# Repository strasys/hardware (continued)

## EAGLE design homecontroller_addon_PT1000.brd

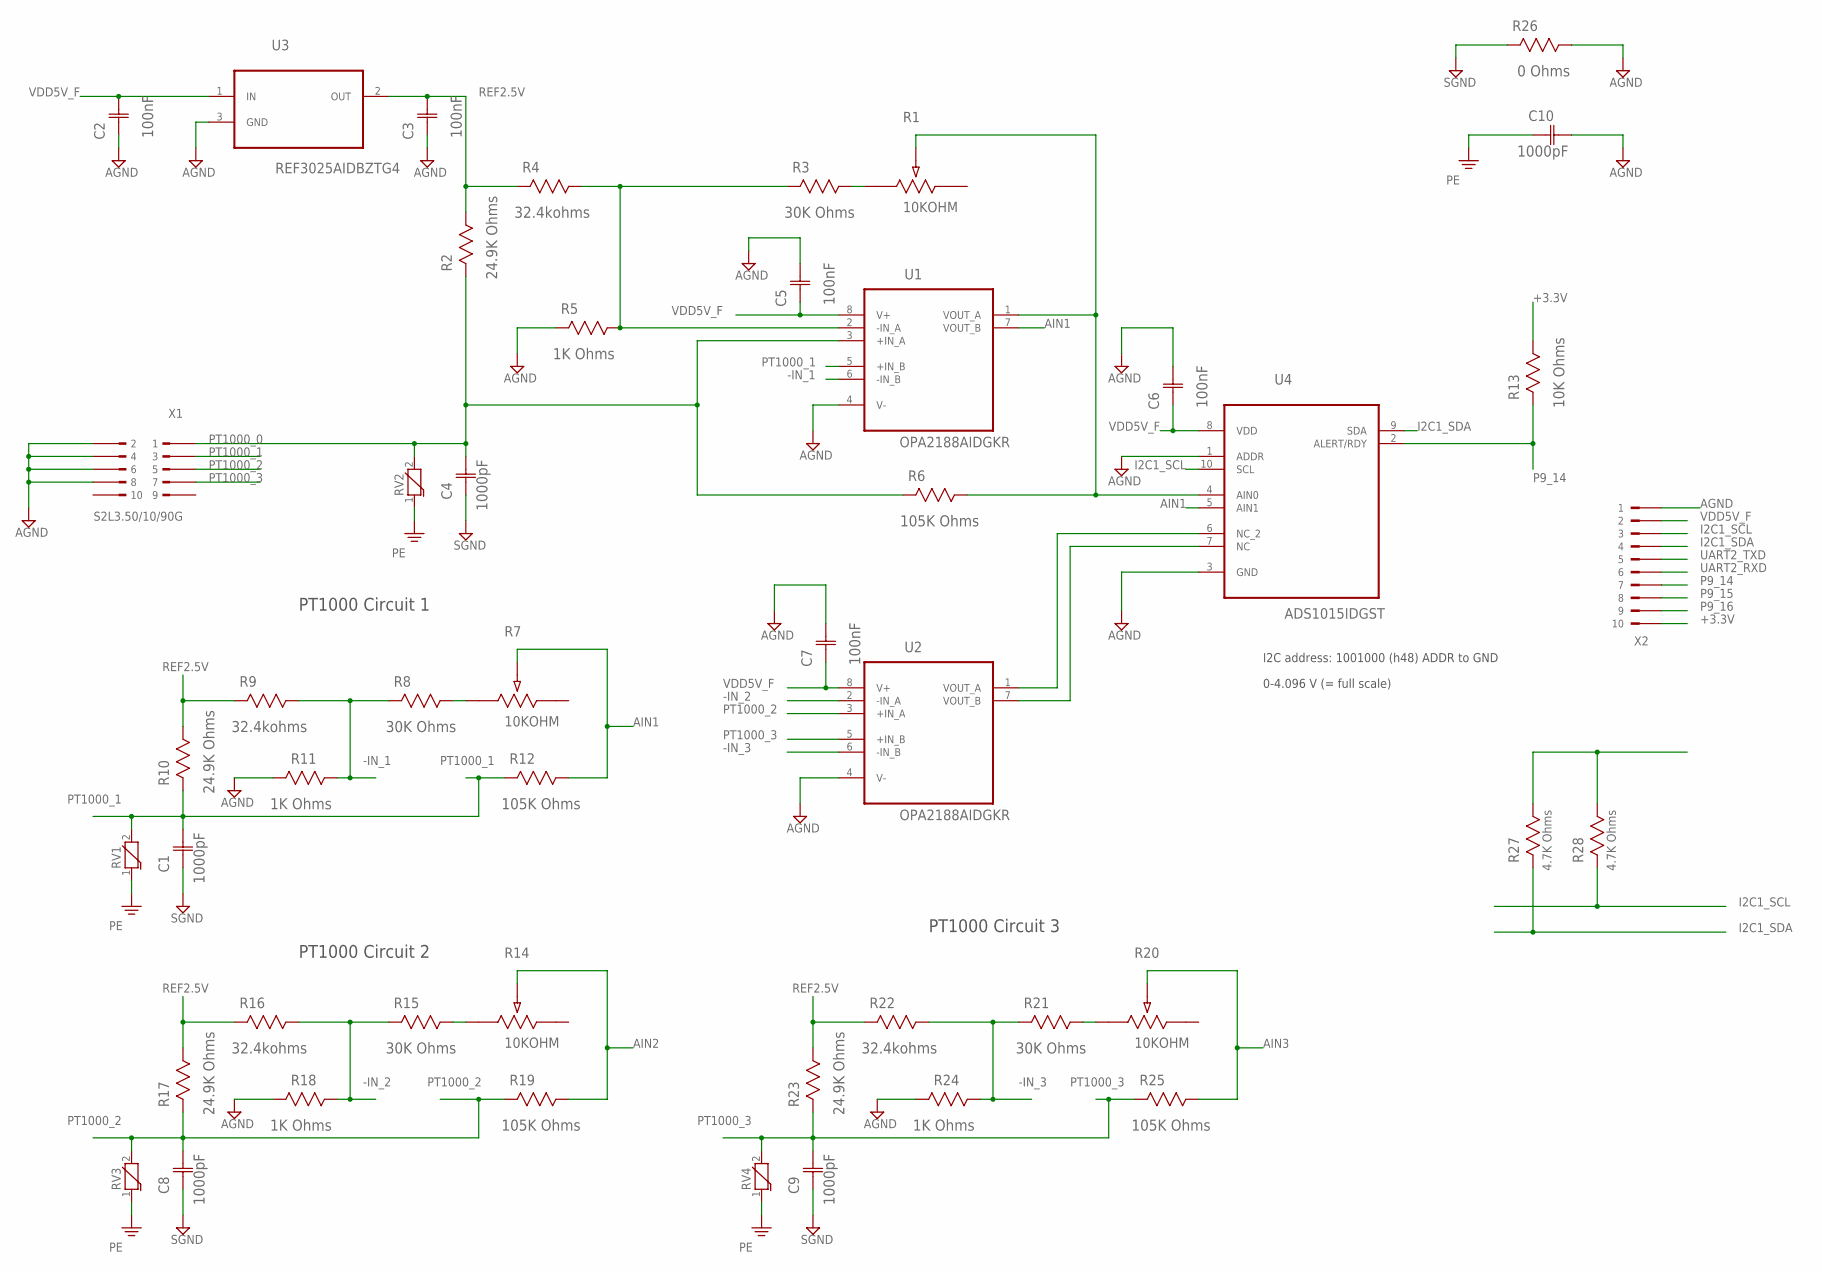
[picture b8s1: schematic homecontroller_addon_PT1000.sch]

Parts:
C1, C4, C8, C9, C10: 1000pF; CAPC3216X88N
C2, C3, C5, C6, C7: 100nF; CAPC2013X110N
R1, R7, R14, R20: 10KOHM; POT_EVM3W
R2, R10, R17, R23: 24.9K Ohms; RESC2013X65N
R3, R8, R15, R21: 30K Ohms; RESC2013X65N
R4, R9, R16, R22: 32.4kohms; RESC2013X65N
R5, R11, R18, R24: 1K Ohms; RESC2013X65N
R6, R12, R19, R25: 105K Ohms; RESC2013X65N
R13: 10K Ohms; RESC2013X65N
R26: 0 Ohms; RESC3216X71N
R27, R28: 4.7K Ohms; RESC2013X65N
RV1, RV2, RV3, RV4: MC-VZ-MCVZ0805M180AGT_0805; WESURGE_0805
U1, U2: OPA2188AIDGKR; SOP65P490X110-8N
U3: REF3025AIDBZTG4; SOT95P237X112-3N
U4: ADS1015IDGST; SOP50P490X110-10N
X1: S2L3.50/10/90G; S2L-90G-10
X2: CON-10X2MM; 2MM-10-THT

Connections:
+3.3V: R13.1, R27.1, R28.1, X2.P$10 (10)
-IN_0: R3.2, R4.1, R5.1, U1.2 (-IN_A)
-IN_1: R8.2, R9.1, R11.1, U1.6 (-IN_B)
-IN_2: R15.2, R16.1, R18.1, U2.2 (-IN_A)
-IN_3: R21.2, R22.1, R24.1, U2.6 (-IN_B)
AGND: C2.1 (C1), C3.1 (C1), C5.2 (C2), C6.2 (C2), C7.2 (C2), C10.2 (C2), R5.2, R11.2, R18.2, R24.2, R26.1, U1.4 (V-), U2.4 (V-), U3.3 (GND), U4.1 (ADDR), U4.3 (GND), X1.2, X1.4, X1.6, X1.8, X2.P$1 (1)
AIN0: R1.2, R6.1, U1.1 (VOUT_A), U4.4 (AIN0)
AIN1: R7.2, R12.1, U1.7 (VOUT_B), U4.5 (AIN1)
AIN2: R14.2, R19.1, U2.1 (VOUT_A), U4.6 (NC_2)
AIN3: R20.2, R25.1, U2.7 (VOUT_B), U4.7 (NC)
I2C1_SCL: R28.2, U4.10 (SCL), X2.P$3 (3)
I2C1_SDA: R27.2, U4.9 (SDA), X2.P$4 (4)
unnamed: R14.1, R15.1
unnamed: R7.1, R8.1
unnamed: R20.1, R21.1
unnamed: R1.1, R3.1
P9_14: R13.2, U4.2 (ALERT/RDY), X2.P$7 (7)
P9_15: X2.P$8 (8)
P9_16: X2.P$9 (9)
PE: C10.1 (C1), RV1.1, RV2.1, RV3.1, RV4.1
PT1000_0: C4.2 (C2), R2.2, R6.2, RV2.2, U1.3 (+IN_A), X1.1
PT1000_1: C1.2 (C2), R10.2, R12.2, RV1.2, U1.5 (+IN_B), X1.3
PT1000_2: C8.2 (C2), R17.2, R19.2, RV3.2, U2.3 (+IN_A), X1.5
PT1000_3: C9.2 (C2), R23.2, R25.2, RV4.2, U2.5 (+IN_B), X1.7
REF2.5V: C3.2 (C2), R2.1, R4.2, R9.2, R10.1, R16.2, R17.1, R22.2, R23.1, U3.2 (OUT)
SGND: C1.1 (C1), C4.1 (C1), C8.1 (C1), C9.1 (C1), R26.2
UART2_RXD: X2.P$6 (6)
UART2_TXD: X2.P$5 (5)
VDD5V_F: C2.2 (C2), C5.1 (C1), C6.1 (C1), C7.1 (C1), U1.8 (V+), U2.8 (V+), U3.1 (IN), U4.8 (VDD), X2.P$2 (2)

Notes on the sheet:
I2C address: 1001000 (h48) ADDR to GND
0-4.096 V (= full scale)
PT1000 Circuit 1
PT1000 Circuit 2
PT1000 Circuit 3

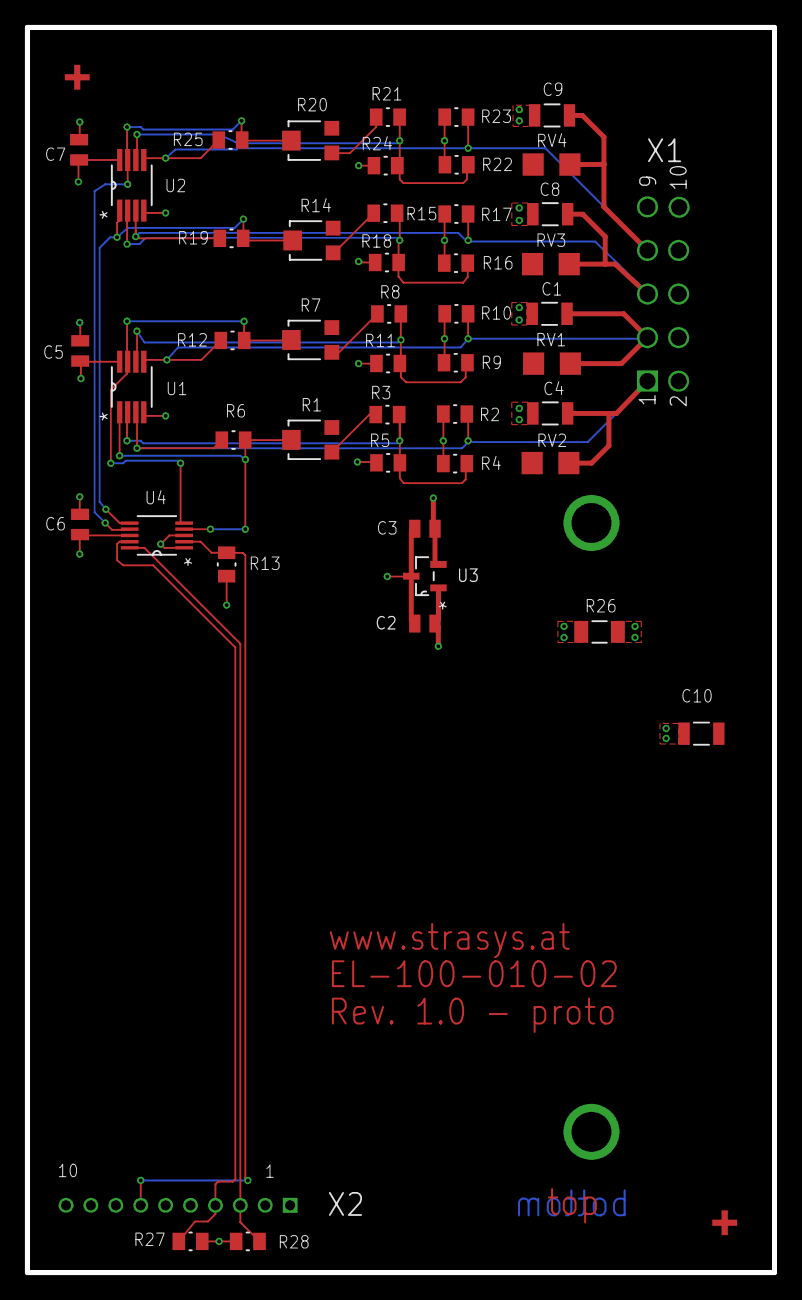
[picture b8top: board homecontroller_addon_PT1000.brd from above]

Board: 4 copper layers, 60.0 x 100.0 mm, 50 parts (0 on the bottom side), 25 nets.

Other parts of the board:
U$1, U$2: PASSER_SMD4

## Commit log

2015-11-24 PT1000 schematics
2015-11-24 lib added
2015-11-29 update lib
2015-11-29 finalised sch
2015-12-01 routing
2015-12-03 update routing
2015-12-04 adopted wire plan
2015-12-05 change position of I2C ADC
2015-12-11 production status
2015-12-11 PCB - production status
2015-12-12 components price opti
2015-12-12 optimisation of BOM
2015-12-17 Simulation data added
2015-12-17 OPA188 lib added
2015-12-17 Analog
2015-12-17 add opa188
2015-12-19 simu opa 170
2015-12-19 PT1000 simu update
2015-12-22 main unit modular unit
2015-12-29 update layout
2015-12-30 Simu
2015-12-30 change to size 9
2016-01-11 simu update
2016-02-04 PT1000 update
2016-02-04 E-cabinet-Tobi
2016-02-11 update PT1000
2016-02-11 LTSpice
2016-02-12 AIN 0-10V optimised
2016-03-13 DIN - Rail
2016-03-25 DIN-rail-controller
2016-03-31 update new design
2016-04-16 new DIN rail hardware
2016-04-17 update DIN rail
2016-04-23 Din rail
2016-04-24 extensions added
2016-05-01 DIN Rail extension
2016-05-09 DIN rail PT1000 and indicator
2016-05-16 prototype order status
2016-05-18 DIN-Rail-production
2016-06-01 e-diagram-pool
2016-06-03 new pool e-circ
2016-07-01 E-Plan-Pool added
